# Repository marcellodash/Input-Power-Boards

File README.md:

# Input Power Boards

Breadboard-compatible board breaks out 9V, 5V, and 3.3V from a 9V battery.

There's a through-hole and a surface mount version, making this a good practice board. 

- <a href="https://github.com/wickerbox/Input-Power-Boards/tree/master/th">TH version</a>
- <a href="https://github.com/wickerbox/Input-Power-Boards/tree/master/smt">SMT version</a>

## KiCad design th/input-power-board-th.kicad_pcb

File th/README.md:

# Input Power Boards

Breadboard-compatible board breaks out 9V, 5V, and 3.3V from a 9V battery.

### Through-Hole v1.1 - Bill of Materials

OSH Park detects a 2 layer board of 1.65x1.03 inches (42x26mm). $8.40 for three. 

|Ref|Qty|Description|MF_Name|MF_PN|Digikey PN|
|---|---|-----------|-------|-----|----------|
|C1|1|CAP CER 0.1UF 50V C0G RADIAL|TDK|FK26C0G1H104J|445-8532-ND|
|C2|1|CAP CER 10UF 25V X7R RADIAL|TDK|FK16X7R1E106K|445-8351-ND|
|J1-J4|4|HEADER MALE 2POS TH 1x02 0.1"|Harwin|M20-9990246|952-2262-ND|
|J1A-J4A|4|CONN TERM SCREW GREEN 2.54MM 2POS TH|OnShoreTech|OSTVN02A150|ED10561-ND|
|J5|1|CONN PWR JACK 2.0X6.5MM HIGH CUR|Panasonic|PJ-202AH|CP-202AH-ND|
|U1|1|IC REG LDO 5V 1A NCP7805 TO220AB|ON Semi|NCP7805TG|NCP7805TGOS-ND|
|U2|1|IC REG LDO 3.3V 1A LD1117 TO220AB|STM|LD1117AV33|497-1485-5-ND|

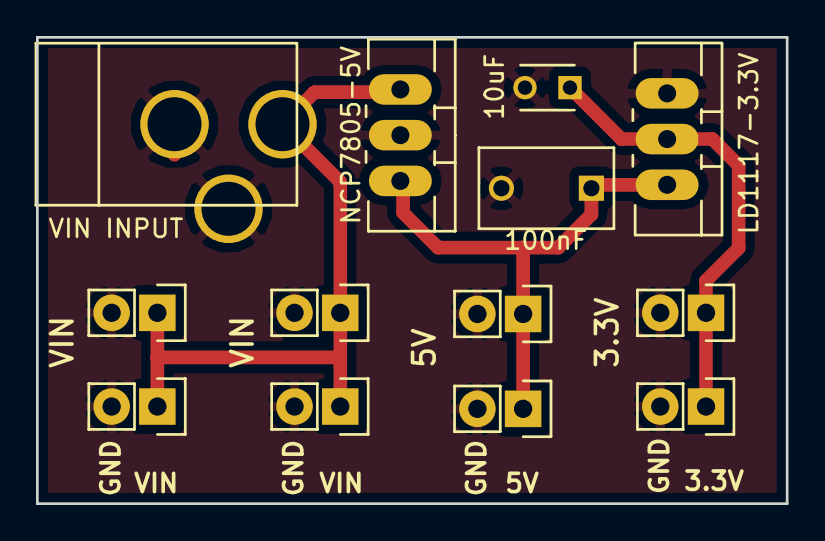
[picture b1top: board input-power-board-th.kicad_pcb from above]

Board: 2 copper layers, 41.7 x 25.9 mm, 13 parts (0 on the bottom side), 4 nets.

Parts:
10uF: 10uF; CAP-DISC-D3MM-P2.5MM
100nF: 100nF; CAP-DISC-D7.5MM-P5MM
J1, J2, J3, J4: HEADER; CONN-HEADER-STRAIGHT-P2.54MM-1x02
J1A1, J2A1, J3A1, J4A1: SCREW; CONN-ONSHORE-SCREW-GREEN-2PIN-TH
LD1117-3.3V: LD1117-3.3V; TO-220-NEUTRAL123-VERT-LONGPADS
NCP7805-5V: NCP7805-5V; TO-220-NEUTRAL123-VERT-LONGPADS
VIN INPUT: BARREL_JACK; CONN-BARREL-JACK-2.5x5.5MM-TH

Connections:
+3V3: 10uF.1, J4.1, J4A1.1, LD1117-3.3V.2
+5V: 100nF.1, J3.1, J3A1.1, LD1117-3.3V.3, NCP7805-5V.3
+9V: J1.1, J1A1.1, J2.1, J2A1.1, NCP7805-5V.1, VIN INPUT.1
GND: 10uF.2, 100nF.2, J1.2, J1A1.2, J2.2, J2A1.2, J3.2, J3A1.2, J4.2, J4A1.2, LD1117-3.3V.1, NCP7805-5V.2, VIN INPUT.2, VIN INPUT.3

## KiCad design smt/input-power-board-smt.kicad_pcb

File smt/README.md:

# Input Power Boards

Breadboard-compatible board breaks out 9V, 5V, and 3.3V from a 9V battery.

### Surface Mount v1.1 - Bill of Materials

OSH Park detects a 2 layer board of 1.53x1.15 inches (39x29mm). $8.70 for three. 

|Ref|Qty|Description|MF_Name|MF_PN|Digikey PN|
|---|---|-----------|-------|-----|----------|
|C1,C2|2|CAP CER 10UF 25V X7R 1210|Taiyo Yuden|TMK325B7106KN-TR|587-2599-1-ND|
|J1-J4|4|HEADER MALE 2POS TH 1x02 0.1"|Harwin|M20-9990246|952-2262-ND|
|J1A-J4A|4|CONN TERM SCREW GREEN 2.54MM 2POS TH|OnShoreTech|OSTVN02A150|ED10561-ND|
|J5|1|CONN PWR JACK 2.0X6.5MM HIGH CUR|Panasonic|PJ-202AH|CP-202AH-ND|
|U1|1|IC REG LDO 5V 1.1A NCP1117 DPAK|ON Semi|NCP1117DT50G|NCP1117DT50GOS-ND|
|U2|1|IC REG LDO 3.3V 1A NCP1117 DPAK|ON Semi|NCP1117DT33G|NCP1117DT33GOS-ND|

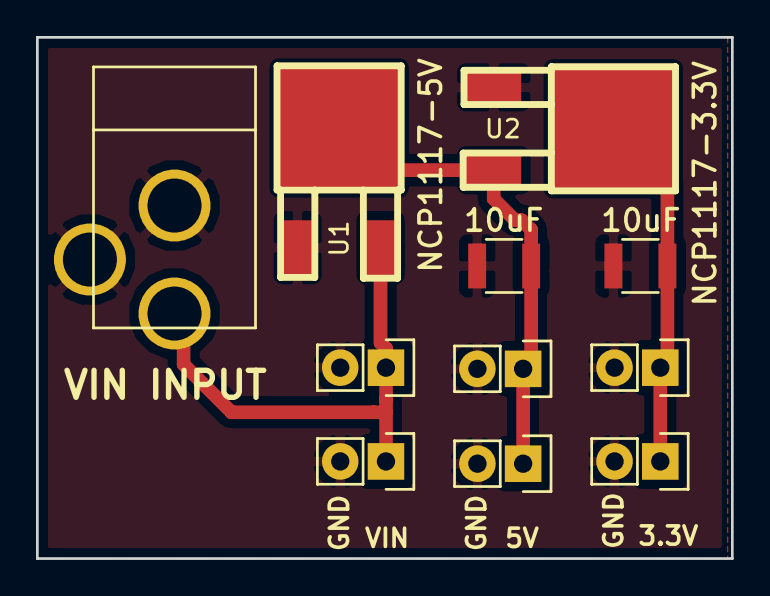
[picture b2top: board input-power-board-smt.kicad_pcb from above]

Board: 2 copper layers, 38.6 x 29.0 mm, 11 parts (0 on the bottom side), 4 nets.

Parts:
C1, C2: 10uF; RLC-1210-SMD
J2, J3, J4: HEADER; CONN-HEADER-STRAIGHT-P2.54MM-1x02
J2A1, J3A1, J4A1: SCREW; CONN-ONSHORE-SCREW-GREEN-2PIN-TH
J5: BARREL_JACK; CONN-BARREL-JACK-2.5x5.5MM-TH
U1: NCP1117-5V; DPAK
U2: NCP1117-3.3V; DPAK

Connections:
+3V3: C2.1, J4.1, J4A1.1, U2.2
+5V: C1.1, J3.1, J3A1.1, U1.2, U2.3
GND: C1.2, C2.2, J2.2, J2A1.2, J3.2, J3A1.2, J4.2, J4A1.2, J5.2, J5.3, U1.1, U2.1
VIN: J2.1, J2A1.1, J5.1, U1.3

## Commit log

2016-07-31 Updated TH version. Ready to order.
2016-07-31 Rename to 'th'.
2016-07-31 Ordering both SMT and TH versions of v1.1.
2016-07-31 Nicer previews.
2016-08-13 Added stencil zip for SMT version.
2016-08-24 Added outline to assembly drawing.
2016-08-30 Cleaning up READMEs.
2016-09-10 Added photos.

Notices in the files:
smt/input-power-board-smt.kicad_pcb:
Released under the CERN Open Hardware License v1.2
